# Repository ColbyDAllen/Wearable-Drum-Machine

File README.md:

# Wearable Drum Machine 

12/15/2024 |

This project is mostly complete. Until I can find a more suitable input/sensory solution, please consider this work on hiatus.

Further information can be found at www.colbydanielallen.com.

4/15/2024 |

This project is still in development. 

On the hardware side, I'm focused on creating more reliable FSR finger sensors.
Weather resistant (magentic charger?) enclosure design is backlogged.

On the circuitry side, I'm designing a custom PCB that incorporates power management, sensor/usb/programmig ports, and an embedded speaker module. 

On the software side there's a number of backlogged tasks. I want to fine-tune / build-out the MIDI looping functionality and create a richer way to sequence these patterns. Variable tempo control in standalone operation (via rotary encoder) is also backlogged.

----

04/01/2024 | Regarding software/code:
Until I've split these up into functional sections, the .ino sketches will build on each other in the following order:
1) FSR Input
2) SMF File Storage
3) MIDI Looper

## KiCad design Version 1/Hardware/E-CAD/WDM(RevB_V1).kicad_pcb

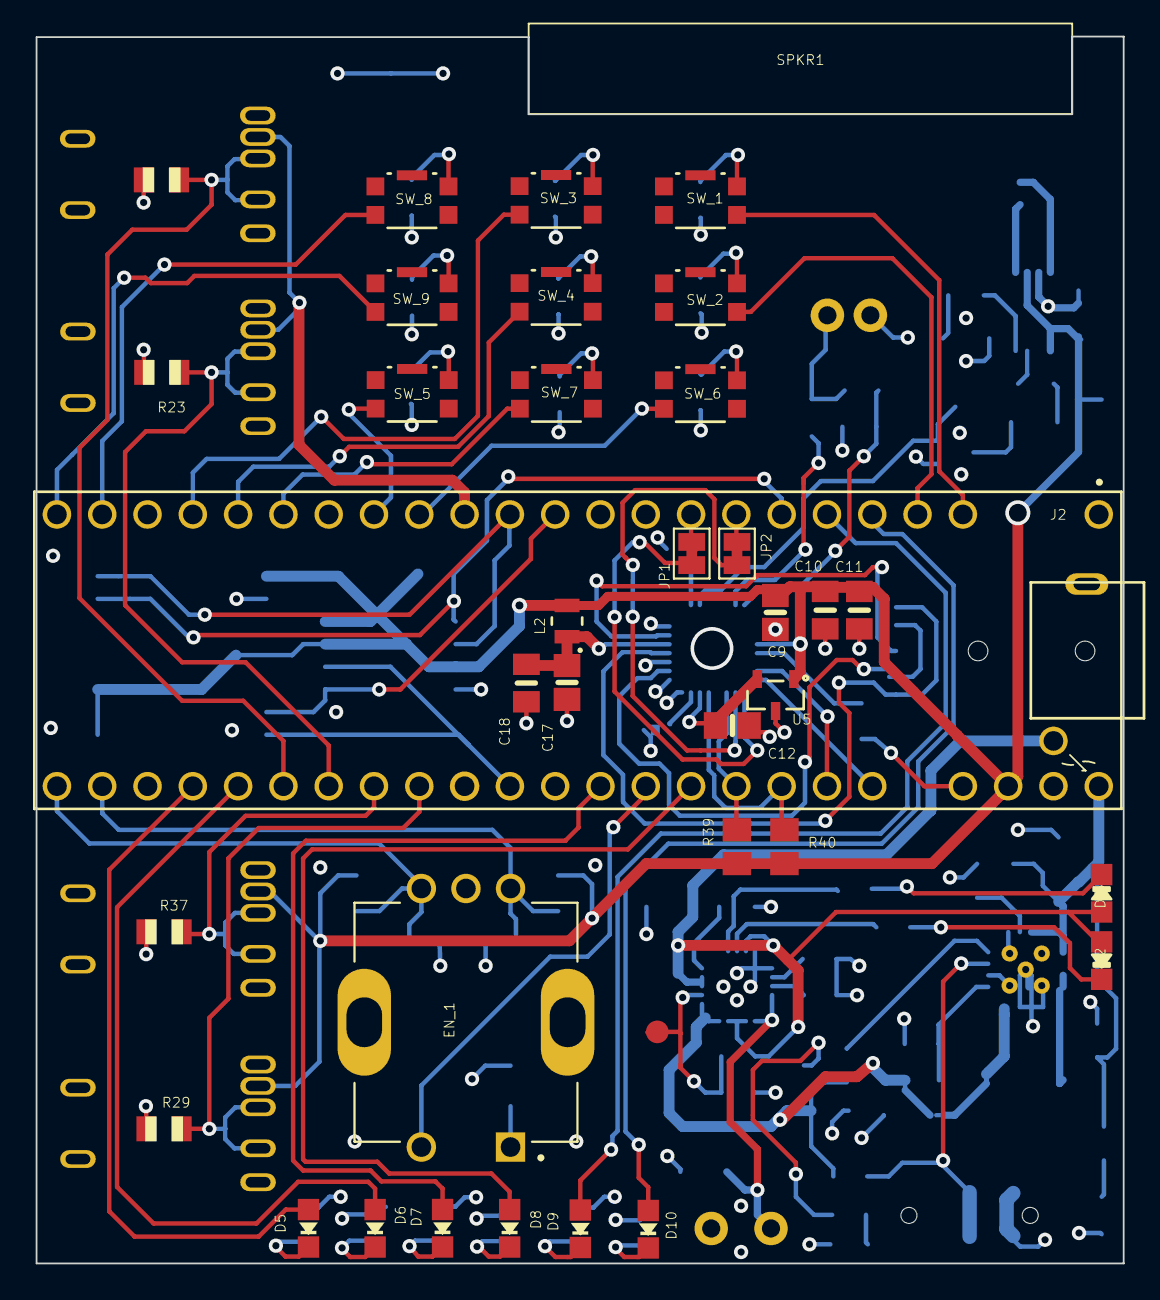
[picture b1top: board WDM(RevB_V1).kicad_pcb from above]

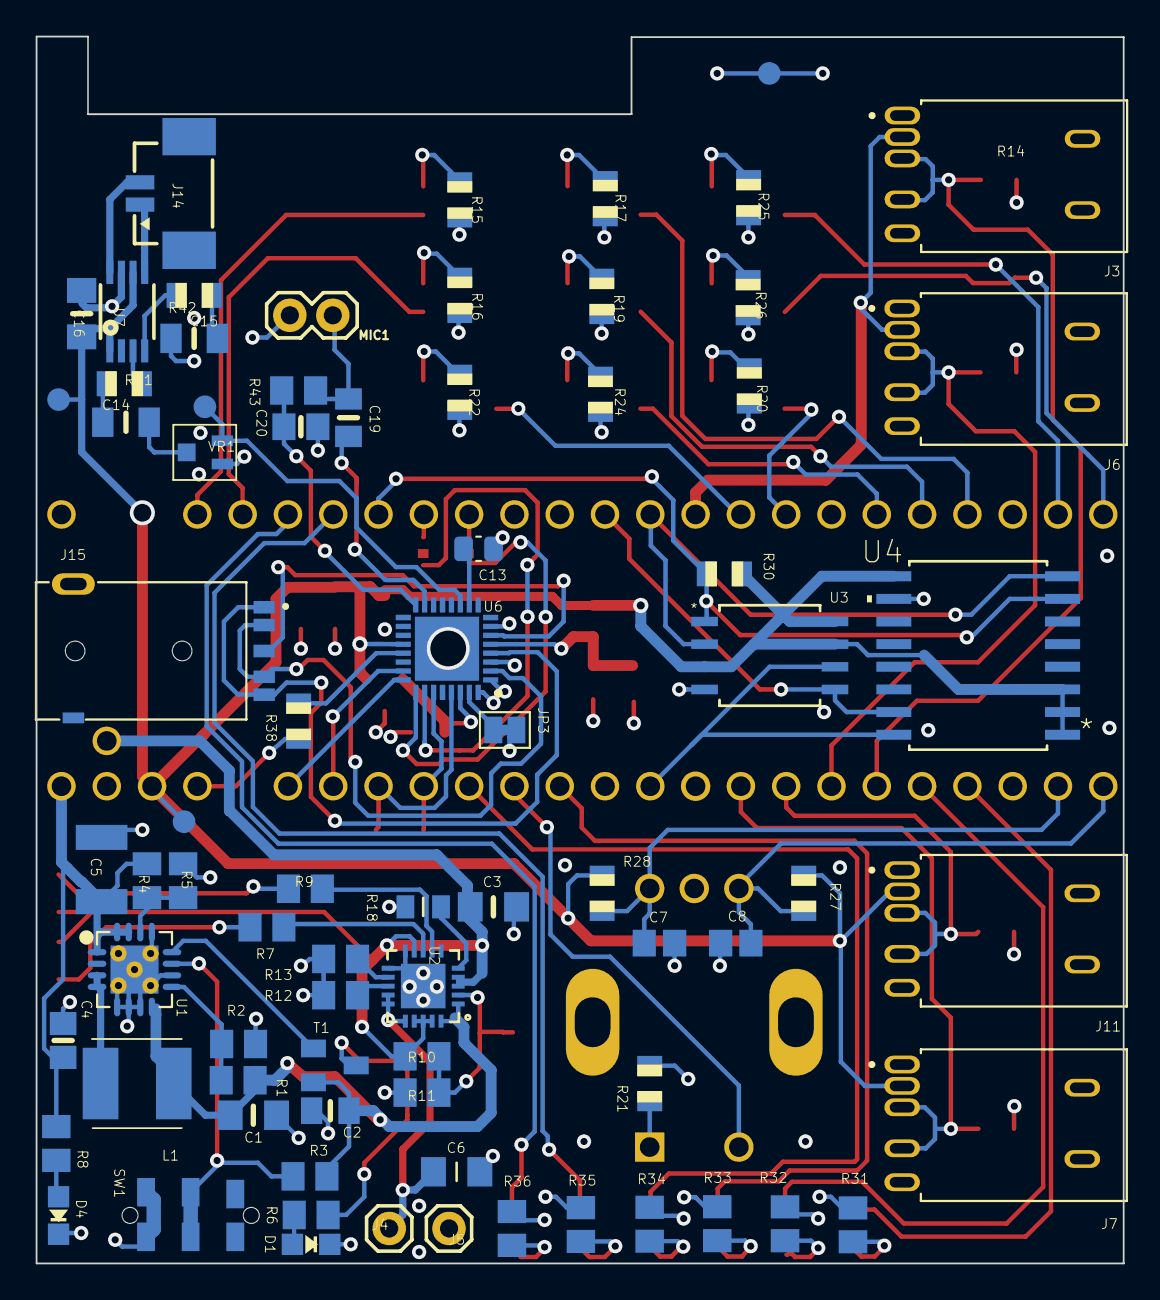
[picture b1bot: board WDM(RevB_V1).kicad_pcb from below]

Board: 4 copper layers, 61.0 x 68.8 mm, 114 parts (77 on the bottom side), 92 nets.

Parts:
C1, C3, C6, C16: 10 uF; C_10uF_0805-NO
C2, C10, C11, C18, C19: 0.1 uF; C_0.1uF_0805_10MGAP
C4, C9, C12, C17, C20: 2.2 uF; C_2.2uF_0805-NO
C5: 100 uF; C_100uF_MLCC_C1210
C7, C8: 100 nF; C_100nF_0805
C13: 0.15 uF; C_0.15uF_0805
C14, C15: 1 uF; C_1uF_0805
D1, D5: RED; CHIPLED_0805_NOOUTLINE
D2: ORANGE; CHIPLED_0805_NOOUTLINE
D3, D6: GREEN; CHIPLED_0805_NOOUTLINE
D4, D8, D10: BLUE; CHIPLED_0805_NOOUTLINE
D7, D9: YELLOW; CHIPLED_0805_NOOUTLINE
EN_1: PEC11R-4215F-S0024; XDCR_PEC11R-4215F-S0024
J2: T4.1; Teensy4.1_Colby(Footprint)
J3, J6, J7, J11: SJ-3542AS-SMT-TR-67; CUI_SJ-3542AS-SMT-TR-67
J4, J5: 1X01_BatteryTerminal_HandSolder
J14: CONN HEADER SMD R/A 2POS 1.25MM; 53398-0271
J15: SJ-3541AS-SMT-TR-67; CUI_SJ-3541AS-SMT-TR-67
JP1, JP2, JP3: JUMPER-SMT_2_NC_TRACE_SILK; SolderJumper-2_P1.3mm_Bridged_Pad1.0x1.5mm
L1: 6.8uH, VLS5045EX-6R8M-H; VLS5045EX330M
L2: 600 OHM, MPZ2012S601AT000; IND_2012_TDK-L
MIC1: POM-5046P-C3310-R; 1X02_TH_
R1, R4: 1.87M; RES_1.87M_0805
R2: 340K; RES_340K_0805
R3, R5: 200K; RES_200K_0805
R6, R7, R8, R9, R12: 1K; RES_1K_0805
R10: 270K; RES_270K_0805
R11, R13: 100K; RES_100K_0805
R14, R15, R16, R17, R19, R20, R21, R22, R23, R24, R25, R26, R27, R28, R29, R30, R37: 10K; RES_10K_R0805
R18: 15K; Thermo_15K_0805-NO
R31, R32, R33, R34, R35, R36, R39, R40, R43: 2.2K; RES_2.2K_0805
R38, R41, R42: 100R; RES_100R_R0805
SPKR1: AdafruitStemmaSpeaker_3923
SW1: JS202011JAQN Slide Switch DPDT Surface Mount, Rig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; JS202011JAQN
SW_1, SW_2, SW_3, SW_4, SW_5, SW_6, SW_7, SW_8, SW_9: KMR211GLFS; PushButton_KMR211_G_LFS_CNK
T1: MMUN2133LT1G; MMUN2133LT1G_SC59-BEC
TP2: VPCC(TP); TestPoint_PAD.03X.05
TP4: +3v3(TP); TestPoint_PAD.03X.05
TP5: GND(TP); TestPoint_PAD.03X.05
TP6: SIG(TP); TestPoint_PAD.03X.05
TP7: +3V3; TestPoint_PAD.03X.05
U1: TPS61090RSAR; TPS61090RSAR_PVQFN-16
U2: MCP73871; MCP73871_QFN20_4MM
U3: W25Q128JVSIQ
U4: S25FL512SAGMFIR13_512MBIT; SO3016_SPA-M
U5: AP7313-18SAG-7
U6: SGTL5000XNBA3R2; QFN50P500X500X90-33N
U7: PAM8302AASCR; MSOP8_0.65MM
VR1: 10K_TC42_Trimpot; TRIMPOT_BOURNS_TC42_2mm_SMD

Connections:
+1V8: C12.1, U5.2 (OUT), U6.30 (VDDD)
+3V3: C9.1, C10.1, C11.1, C16.1, J2.T3.3V (3.3V), J3.3, J6.3, J7.3, J11.3, L2.2, R27.1, R28.1, R30.2, R39.2, R40.2, TP4.P$1 (1), TP7.P$1 (1), U3.3 (~WP(IO2)), U3.7 (~HOLD(IO3)), U3.8 (VCC), U4.1 (~HOLD/IO3), U4.2 (VCC), U4.3 (~RESET/RFU), U4.9 (~WP/IO2), U5.1 (IN), U6.20 (VDDIO), U7.1 (/SD), U7.6 (VDD)
+5V: C4.1, C5.1, J2.+5V (VIN), R4.1, R8.1, U1.1 (VOUT), U1.15 (VOUT), U1.16 (VOUT)
/ FSRpin_1_A14: J2.38 (38_CS1_IN1), J3.2, J3.5, R14.1
/ FSRpin_2_A15: J2.39 (39_MISO1_OUT1A), J6.2, J6.5, R23.1
/ FSRpin_3_A16: J2.40 (40_A16), J11.2, J11.5, R37.1
/ FSRpin_4_A17: J2.41 (41_A17), J7.2, J7.5, R29.1
/ECHOPin: J2.24 (24_A10_TX6_SCL2), SW_6.3
/ENABLE: R3.2, SW1.2, SW1.5, U1.11 (EN)
/LBO: T1.B, U1.12 (LBO)
/PLAYledPin: D6.A, J2.37 (37_CS)
/Pin6: J2.6 (6_OUT1D), R30.1, U3.1 (~CS), U4.7 (~CS)
/Pin7: J2.7 (7_RX2_OUT1A), JP2.1
/Pin8: J2.8 (8_TX2_IN1), JP1.1
/Pin11: J2.11 (11_MOSI_CTX1), U3.5 (DI(IO0)), U4.15 (SI/IO0)
/Pin12: J2.12 (12_MISO_MQSL), U3.2 (DO(IO1)), U4.8 (SO/IO1)
/Pin13: J2.13 (13_SCK_LED), U3.6 (CLK), U4.16 (SCK)
/Pin20: J2.20 (20_A6_TX5_LRCLK1), U6.23 (I2S_LRCLK)
/Pin21: J2.21 (21_A7_RX5_BCLK1), U6.24 (I2S_SCLK)
/Pin23: J2.23 (23_A9_CRX1_MCLK1), R38.1
/RECPin: J2.32 (32_OUT1B), SW_9.3
/SCL: J2.19 (19_A5_SCL), R40.1, U6.29 (CTRL_CLK)
/SDA: J2.18 (18_A4_SDA), R39.1, U6.27 (CTRL_DATA)
/SPKR+: J14.1, U7.5 (VO_P)
/SPKR-: J14.2, U7.8 (VO_N)
/Sig: TP6.P$1 (1), U6.11 (LINEOUT_R), VR1.3 (E)
/VDDA: C17.1, C18.1, L2.1, U6.5 (VDDA)
/VPCC(TP): R10.2, R11.1, TP2.P$1 (1), U2.P$2 (VPCC)
/clockTrigPin: J2.27 (27_A13_SCK1), SW_7.3
/optAPin: C7.2, EN_1.A, J2.34 (34_RX8), R28.2
/optBPin: C8.2, EN_1.B, J2.33 (33_MCLK2), R27.2
/pushRotaryPin: EN_1.2, J2.16 (16_A2_RX4_SCL1)
/startPin: J2.31 (31_CTX3), SW_8.3
/trackLEDPin_1: D7.A, J2.15 (15_A1_RX3_SPDIF_IN)
/trackLEDPin_2: D8.A, J2.17 (17_A3_TX4_SDA1)
/trackLEDPin_3: D9.A, J2.5 (5_IN2)
/trackLEDPin_4: D10.A, J2.4 (4_BCLK2)
/trackPin_1: J2.28 (28_RX7), SW_4.3
/trackPin_2: J2.29 (29_TX7), SW_3.3
/trackPin_3: J2.3 (3_LRCLK2), SW_2.2
/trackPin_4: J2.2 (2_OUT2), SW_1.2
/undoPin: J2.25 (25_A11_RX6_SDA2), SW_5.3
/ RECLEDPin: D5.A, J2.36 (36_CS)
GND: C1.2, C2.2, C3.1, C4.2, C5.2, C6.2, C7.1, C8.1, C9.2, C10.2, C11.2, C12.2, C13.2, C15.2, C16.2, C17.2, C18.2, C20.2, D1.C, D4.C, EN_1.C, J2.GND_0, J2.GND_1, J2.GND_2, J3.1, J3.4, J5.1, J6.1, J6.4, J7.1, J7.4, J11.1, J11.4, JP3.1, MIC1.2, R2.2, R5.2, R11.2, R12.2, R13.2, R14.2, R15.1, R16.1, R17.1, R18.2, R19.1, R20.1, R21.2, R22.1, R23.2, R24.1, R25.1, R26.1, R29.2, R31.2, R32.2, R33.2, R34.2, R35.2, R36.2, R37.2, SW1.3, SW1.6, TP5.P$1 (1), U1.5 (PGND), U1.6 (PGND), U1.7 (PGND), U1.10 (SYNC), U1.13 (GND), U1.P$18 (PAD), U1.P$19 (PAD), U1.P$20 (PAD), U1.P$21 (PAD), U1.P$22 (PAD), U1.THERMAL (PAD), U2.P$10 (VSS1), U2.P$11 (VSS2), U2.P$21 (EP), U3.4 (GND), U4.10 (VSS), U5.3 (GND), U6.1 (GND_1), U6.3 (GND_2), U6.7 (AGND), U6.32 (CTRL_MODE), U6.33 (GND_3), U7.7 (GND), VR1.1 (A)
unnamed: C14.1, R41.1
unnamed: C15.1, R42.1
unnamed: C19.2, MIC1.1, R43.2
unnamed: D1.A, R6.2
unnamed: D2.C, R7.1
unnamed: D3.C, R9.1
unnamed: D4.A, R8.2
unnamed: D5.C, R31.1
unnamed: D6.C, R32.1
unnamed: D7.C, R33.1
unnamed: D8.C, R34.1
unnamed: D9.C, R35.1
unnamed: D10.C, R36.1
unnamed: EN_1.1, R21.1
unnamed: L1.2, U1.3 (SW), U1.4 (SW)
unnamed: R6.1, T1.C
unnamed: R15.2, SW_1.1
unnamed: R16.2, SW_2.1
unnamed: R17.2, SW_3.1
unnamed: R19.2, SW_4.1
unnamed: R20.2, SW_5.1
unnamed: R22.2, SW_6.1
unnamed: R24.2, SW_7.1
unnamed: R25.2, SW_8.1
unnamed: R26.2, SW_9.1
unnamed: R4.2, R5.1, U1.14 (FB)
unnamed: R1.2, R2.1, U1.9 (LBI)
unnamed: R12.1, U2.P$13 (PROG1)
unnamed: R13.1, U2.P$12 (PROG3)
unnamed: R7.2, U2.P$8 (STAT1/LBO)
unnamed: R9.2, U2.P$7 (STAT2)
unnamed: R18.1, U2.P$5 (THERM)
unnamed: JP3.2, U6.31 (CTRL_ADR0_CS)
unnamed: J15.3, U6.6 (HP_L)
unnamed: J15.2, J15.5, U6.2 (HP_R)
unnamed: J15.1, J15.4, U6.4 (HP_VGND)
unnamed: JP2.2, U6.26 (I2S_DIN)
unnamed: JP1.2, U6.25 (I2S_DOUT)
unnamed: C19.1, U6.15 (MIC)
unnamed: C20.1, R43.1, U6.16 (MIC_BIAS)
unnamed: R38.2, U6.21 (SYS_MCLK)
unnamed: C13.1, U6.10 (VAG)
unnamed: R42.2, U7.4 (IN_N)
unnamed: R41.2, U7.3 (IN_P)
unnamed: C14.2, VR1.2 (S)
VBUS: C3.2, D2.A, D3.A, J2.49 (VUSB), R10.1, U2.P$3 (SEL), U2.P$4 (PROG2), U2.P$9 (/TE), U2.P$17 (CE), U2.P$18 (VIN1), U2.P$19 (VIN2)
VLIPO: C6.1, J4.1, U2.P$14 (VBAT1), U2.P$15 (VBAT2), U2.P$16 (VBATSENS)
V_Batt: C1.1, C2.1, L1.1, R1.1, R3.1, T1.E, U1.8 (VBAT), U2.P$1 (VOUT1), U2.P$20 (VOUT2)

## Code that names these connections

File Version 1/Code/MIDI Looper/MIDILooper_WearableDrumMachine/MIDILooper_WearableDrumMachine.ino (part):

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// ======================================================================================

// Sequencer Pin Assignment
const byte RECPin = 32;   
const byte startPin = 31; 
const byte clockTrigPin = 27;  
const byte pushRotaryPin = 16; 
/*const byte ECHOPin = 27;*/
const byte ECHOPin = 24; 
const byte undoPin = 25;

// Track Selection Pin Assignment
const byte trackPin[MAX_TRACKS] = { 28, 29, 3, 2 };  

// Variable Tempo Pin Assignment
const byte optAPin = 34;
const byte optBPin = 33;

// Record & Playback LED Pin Assignment
const byte RECLEDPin = 36;
const byte PLAYledPin = 37;

// Track Selection LED Pin Assignment
const byte trackLEDPin[MAX_TRACKS] = { 15, 17, 5, 4 };
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  mixer1.gain(2, 0.4);
  mixer1.gain(3, 0.4);

  pinMode(RECPin, INPUT_PULLUP);
  pinMode(startPin, INPUT_PULLUP);
  pinMode(pushRotaryPin, INPUT_PULLUP);
  pinMode(optAPin, INPUT_PULLUP);
  pinMode(optBPin, INPUT_PULLUP);
  pinMode(ECHOPin, INPUT_PULLUP);
  pinMode(undoPin, INPUT_PULLUP);
  pinMode(clockTrigPin, INPUT_PULLUP);
  for (int i = 0; i < MAX_TRACKS; i++) { 
    pinMode(trackPin[i], INPUT_PULLUP);
  }
  pinMode(RECLEDPin, OUTPUT);
  pinMode(PLAYledPin, OUTPUT);
  for (int j = 0; j < MAX_TRACKS; j++) { 
    pinMode(trackLEDPin[j], OUTPUT); 
  }
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    PLAY = true;
    FULL_PANIC();
    FULL_LED_Blink(5);
    digitalWrite(PLAYledPin, HIGH);
    digitalWrite(trackLEDPin[0], HIGH);
    currentTrack = 0;
    currentSequence = 0;
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    beatLenght = 500000; 
    prevBeatLenght = beatLenght;
    timeFrame = 16; 
    RECState = digitalRead(RECPin);
    undoState = digitalRead(undoPin);
    optA_state = digitalRead(optAPin);
    ECHOState = digitalRead(ECHOPin);   
    startState = digitalRead(startPin);
    clockTrigState = digitalRead(clockTrigPin);

    // Track Initialization
    for (int l = 0; l < MAX_TRACKS; l++) {      
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  */
  void Handle_Start() {
    PLAY = true;
    digitalWrite(PLAYledPin, HIGH);
    for (int i = 0; i < MAX_SEQUENCES; i++) {
      noteSeqCounter[i] = 0;
    }
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  */
  void Handle_Stop() {
    PLAY = false;
    digitalWrite(PLAYledPin, LOW);
    FULL_PANIC();
  }
// ======================================================================================
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  Clock Trigger Function:
*/
  void clockTrigSwitch() {
    if (digitalRead(clockTrigPin) != clockTrigState /*&& millis()-trigTime > debounceTime*/) {
      clockTrigState = !clockTrigState;
      if (clockTrigState == HIGH) {
        trigCount++;
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    Record Switch Function:
  */
  void REC_Switch() {
    if (digitalRead(RECPin) != RECState && millis() - trigTime > debounceTime) {
      RECState = !RECState;
      trigTime = millis();
      if (RECState == LOW) {
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    Echo ("Panic") Function:
  */
  void ECHO_Switch() {           
    if (digitalRead(ECHOPin) != ECHOState && millis() - trigTime > debounceTime) {
      ECHOState = !ECHOState;
      trigTime = millis();
      if (ECHOState == LOW) {
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    Undo Button Function:
  */
  void Undo_Switch() {
    if (digitalRead(undoPin) != undoState && millis() - trigTime > debounceTime) {
      undoState = !undoState;
      trigTime = millis();
      if (undoState == LOW) {
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    Play Button Function:
  */
  void Play_Switch() {   
    if (digitalRead(startPin) != startState && millis() - trigTime > debounceTime) { 
      startState = !startState;
      trigTime = millis();
      if (startState == LOW) {
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    Metronome On/Off (Encoder Push Button) Function:
  */
  void Metronome_Switch() {
    if (digitalRead(pushRotaryPin) != pushRotaryState && millis() - trigTime > debounceTime) {
      pushRotaryState = !pushRotaryState;
      trigTime = millis();
      if (pushRotaryState == LOW) {
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  */
  void Opt_Encoder() {
    if (incomingClock == 0) {
      if (digitalRead(optAPin) != optA_state && millis() - trigTime > rotaryDebounceTime) {  
        optA_state = !optA_state;  
        trigTime = millis();    
        if (optA_state == HIGH) {
          if (digitalRead(optBPin) == HIGH) {
            beatLenght = beatLenght - 10000; 
          } 
          else {
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  void FULL_LED_Blink(byte count) {
    for (int i = 0; i < count; i++) {
      digitalWrite(RECLEDPin, HIGH);
      digitalWrite(PLAYledPin, HIGH);
      for (int j = 0; j < MAX_TRACKS; j++) {
        digitalWrite(trackLEDPin[j], HIGH);
      }
      delay(200);                                
      digitalWrite(RECLEDPin, LOW);
      digitalWrite(PLAYledPin, LOW);
      for (int k = 0; k < MAX_TRACKS; k++) {
        digitalWrite(trackLEDPin[k], LOW);
      }
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
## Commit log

2024-03-24 Create Code
2024-03-24 Create Hardware
2024-03-24 Create MIDI Looper
2024-03-24 Add files via upload
    Combined MIDI Looper, SMF File Storage, and FSR Input code
2024-03-25 Create Schematics
2024-04-02 Create F3Ds
2024-04-13 README-STLs.md
    Specifies 3D printing filament used for each part
2024-05-21 Added KiCad WDM(RevB_1) project files
2024-05-21 Added reference PDF & PNGs for review
2024-05-21 Updated PCB zones & board outline. Also uploaded revised pin definitions to match routing
2024-05-21 Deleted outdated midilooper.ino
2024-05-21 Added symbol and footprint libraries to KiCad files
2024-05-21 Added 3D models to Kicad files
2024-05-26 Added Gerber & Drill files
2025-01-17 Delete Version 2/Hardware/MCAD Files/Bottom_Enclosure_WDM(RevB)_4.3.STL
    Renamed for clarity and reuploaded.
2025-01-17 Delete Version 2/Hardware/MCAD Files/ButtonActuators_WDM(RevB)_4.3.STL
    Renamed for clarity and reuploaded.
2025-01-17 Delete Version 2/Hardware/MCAD Files/Top_Enclosure_WDM(RevB)_4.3.STL
    Renamed for clarity and reuploaded.
2025-03-07 Add files via upload
    - Modularized the monolith from version 1
    - Added flash logic for handling alternative samples
